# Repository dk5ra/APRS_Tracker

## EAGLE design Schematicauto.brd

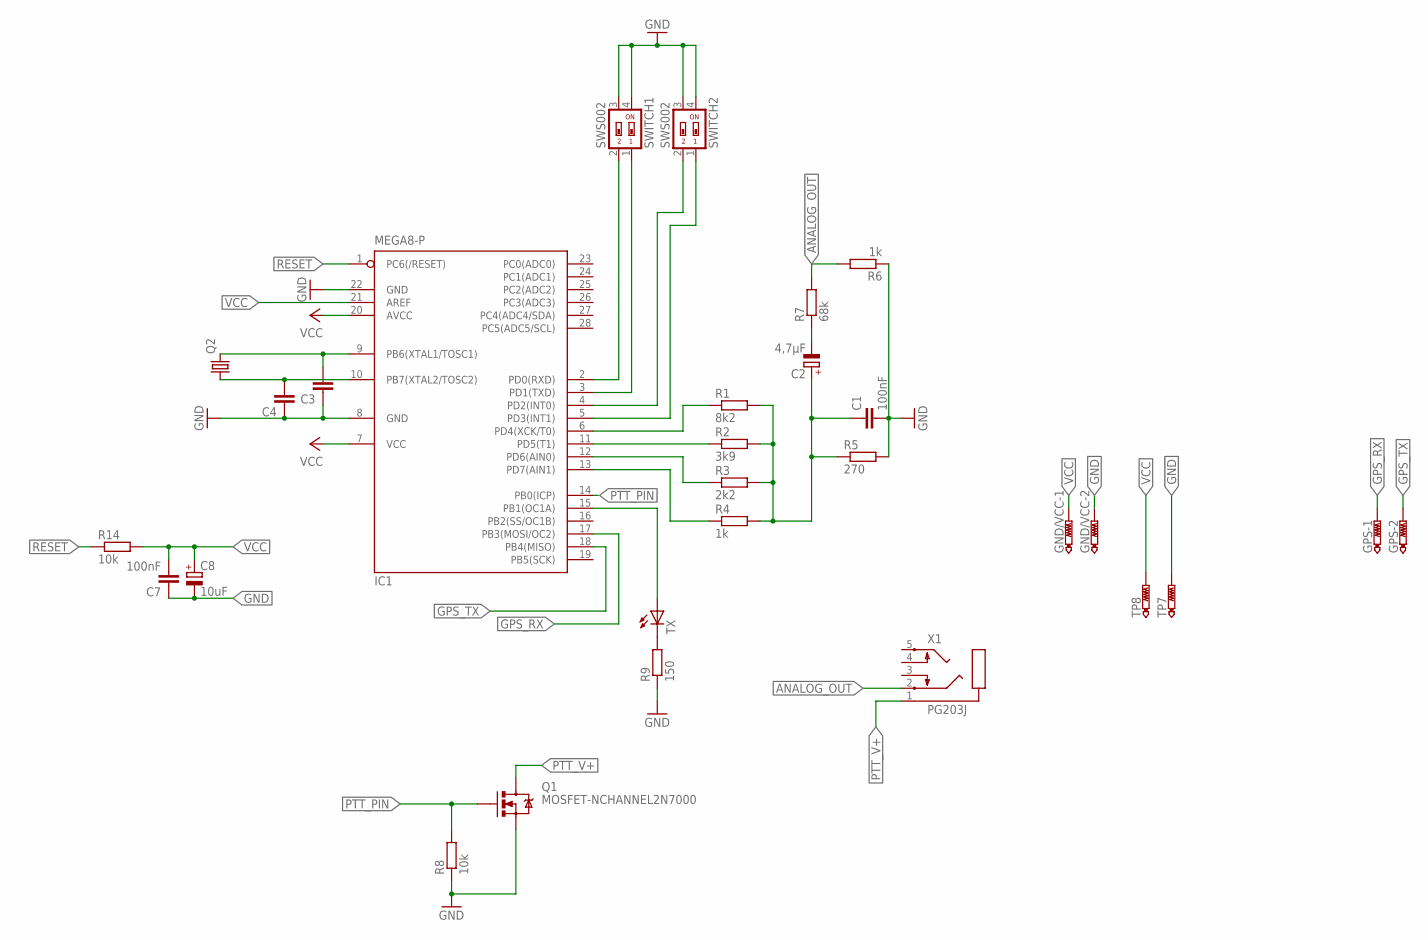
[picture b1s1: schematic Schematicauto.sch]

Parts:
C1: 100nF; C025-025X050
C2: 4,7µF; E2-4
C3, C4: C-EU025-025X050; C025-025X050
C7: 100nF; C050-030X075
C8: 10uF; TT5D9
GND/VCC: PTR2; P2-38-17
GPS: PTR2; P2-38-17
IC1: MEGA8-P; DIL28-3
Q1: MOSFET-NCHANNEL2N7000; TO-92
Q2: CRYSTALHC49S; HC49/S
R1: 8k2; 0207/12
R2: 3k9; 0207/12
R3: 2k2; 0207/12
R4, R6: 1k; 0207/12
R5: 270; 0207/12
R7: 68k; 0207/12
R8, R14: 10k; 0207/12
R9: 150; 0207/12
SWITCH1, SWITCH2: SWS002; SMS-002
TP7, TP8: PTR1PAD1-20Y; P1-20Y
TX: LED5MM
X1: PG203J

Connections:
ANALOG_OUT: R6.2, R7.2, X1.2
GND: C1.2, C3.1, C4.1, C7.1, C8.-, GND/VCC.TP-2, IC1.8 (GND), IC1.22 (GND), Q1.1 (S), R5.2, R6.1, R8.1, R9.1, SWITCH1.3, SWITCH1.4, SWITCH2.3, SWITCH2.4, TP7.TP
GPS_RX: GPS.TP-1, IC1.17 (PB3(MOSI/OC2))
GPS_TX: GPS.TP-2, IC1.18 (PB4(MISO))
unnamed: IC1.6 (PD4(XCK/T0)), R1.1
unnamed: IC1.11 (PD5(T1)), R2.1
unnamed: IC1.12 (PD6(AIN0)), R3.1
unnamed: IC1.13 (PD7(AIN1)), R4.1
unnamed: C1.1, C2.+, R1.2, R2.2, R3.2, R4.2, R5.1
unnamed: C2.-, R7.1
unnamed: IC1.15 (PB1(OC1A)), TX.A
unnamed: IC1.2 (PD0(RXD)), SWITCH1.2
unnamed: IC1.3 (PD1(TXD)), SWITCH1.1
unnamed: R9.2, TX.K (C)
unnamed: IC1.4 (PD2(INT0)), SWITCH2.2
unnamed: IC1.5 (PD3(INT1)), SWITCH2.1
unnamed: C4.2, IC1.10 (PB7(XTAL2/TOSC2)), Q2.1
unnamed: C3.2, IC1.9 (PB6(XTAL1/TOSC1)), Q2.2
PTT_PIN: IC1.14 (PB0(ICP)), Q1.2 (G), R8.2
PTT_V+: Q1.3 (D), X1.1
RESET: IC1.1 (PC6(/RESET)), R14.1
VCC: C7.2, C8.+, GND/VCC.TP-1, IC1.7 (VCC), IC1.20 (AVCC), IC1.21 (AREF), R14.2, TP8.TP

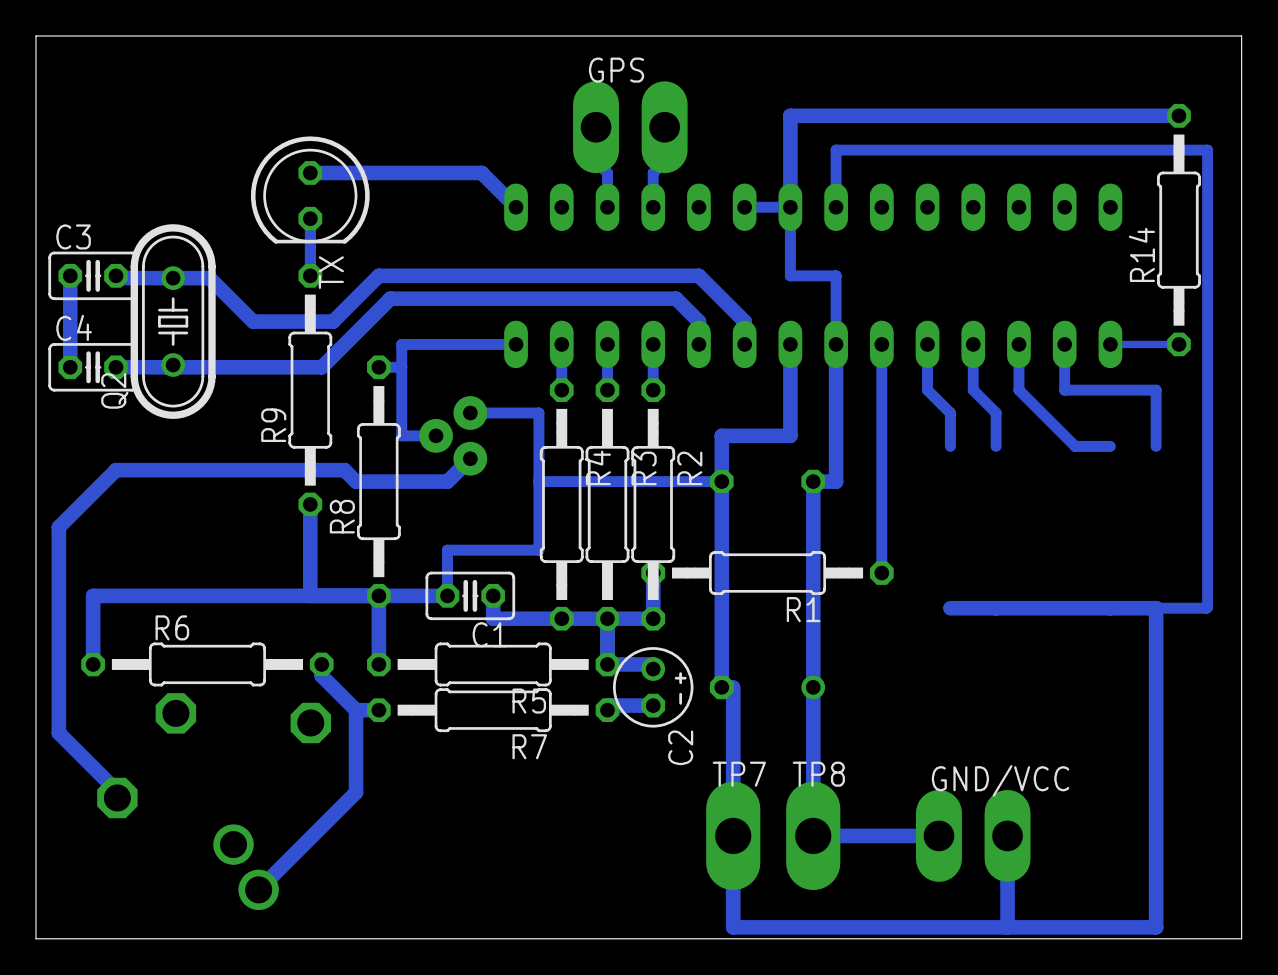
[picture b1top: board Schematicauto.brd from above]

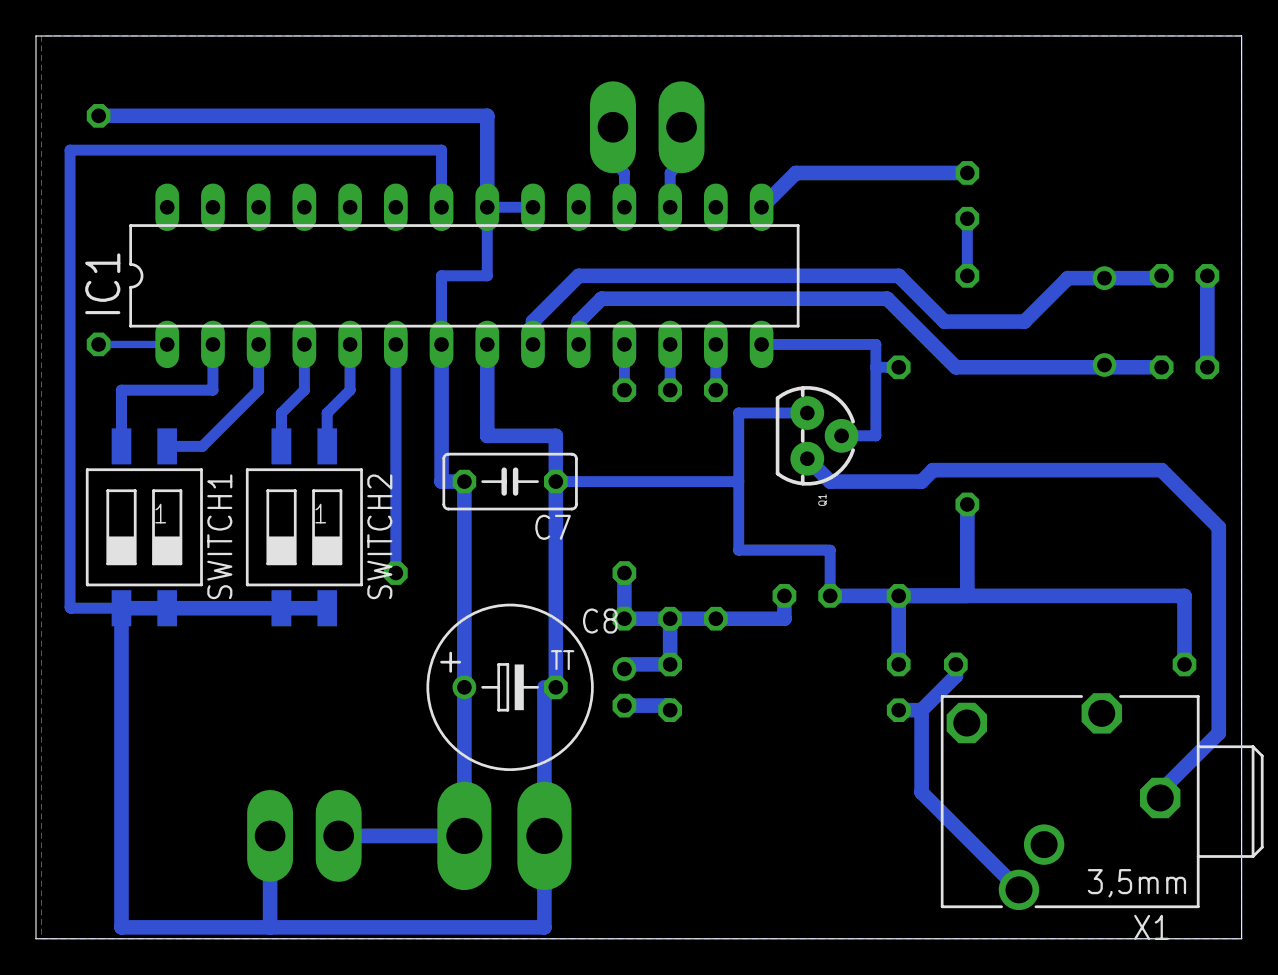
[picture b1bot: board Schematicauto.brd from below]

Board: 2 copper layers, 67.0 x 50.2 mm, 27 parts (7 on the bottom side), 22 nets.

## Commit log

2017-02-12 init push
2018-10-29 sanatize markup

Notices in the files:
parts and their libraries:
SparkFun-DiscreteSemi: Licensing: Creative Commons ShareAlike 4.0 International - https://creativecommons.org/licenses/by-sa/4.0
